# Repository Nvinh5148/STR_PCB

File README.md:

# STR_PCB

Custom PCB design for the low-level controller of the STR Robot autonomous vehicle platform.

## Overview

This repository contains the hardware design files for the custom controller board used in the STR Robot project. The board is designed to interface with the STM32-based firmware layer and provide the electrical bridge between the vehicle hardware and the ROS 2 autonomy stack.

This repository is part of the complete STR Robot simulation-to-reality system:
- custom PCB hardware
- STM32 micro-ROS firmware
- ROS 2 autonomy workspace
- real-world Ackermann robot deployment

## Board Preview

## Schematic Preview

**Schematic PDF:** [schematicf4.pdf](https://github.com/user-attachments/files/26848001/schematicf4.pdf)

## Repository Contents

- `f4_v2.kicad_sch` — KiCad schematic
- `f4_v2.kicad_pcb` — KiCad PCB layout
- `f4_v2.kicad_pro` — KiCad project file
- `Gerber_f4_v2/` — exported Gerber manufacturing files
- `Gerber_f4_v2.zip` — compressed Gerber package
- `f4_v2-backups/` — backup files

## Purpose

The board is designed as the low-level control hardware for the STR Robot platform. It supports the embedded controller responsible for:
- motor-related interfaces
- steering-related interfaces
- encoder and GPIO connections
- serial communication interfaces
- integration with the STM32 micro-ROS firmware layer

## System Role

This repository corresponds to the **hardware layer** of the full robot system:

`STR_PCB` → `microros_ws` → `ttbot_ws`

- **STR_PCB**: custom controller board
- **microros_ws**: STM32-based embedded firmware using micro-ROS
- **ttbot_ws**: high-level ROS 2 workspace for localization, planning, and navigation

## Hardware Interfaces

From the current board design, the PCB provides grouped connectors for:
- **GPIO**
- **ENCODER**
- **MOTOR**
- **UART / serial communication**
- power input / output terminals

## Toolchain

- KiCad for schematic and PCB design
- Standard Gerber export for PCB fabrication

## Manufacturing

To fabricate the board:
1. Open the project in KiCad
2. Review the schematic and PCB layout
3. Export or use the provided Gerber files in `Gerber_f4_v2/`
4. Submit the Gerber package to your PCB manufacturer

## Related Repositories

- Firmware: [`microros_ws`](https://github.com/Nvinh5148/microros_ws)
- ROS 2 autonomy stack: [`ttbot_ws`](https://github.com/Uyle-gif/ttbot_ws)

## Project Context

This board is part of the STR Robot simulation-to-reality development pipeline for an Ackermann-steered autonomous mobile robot.

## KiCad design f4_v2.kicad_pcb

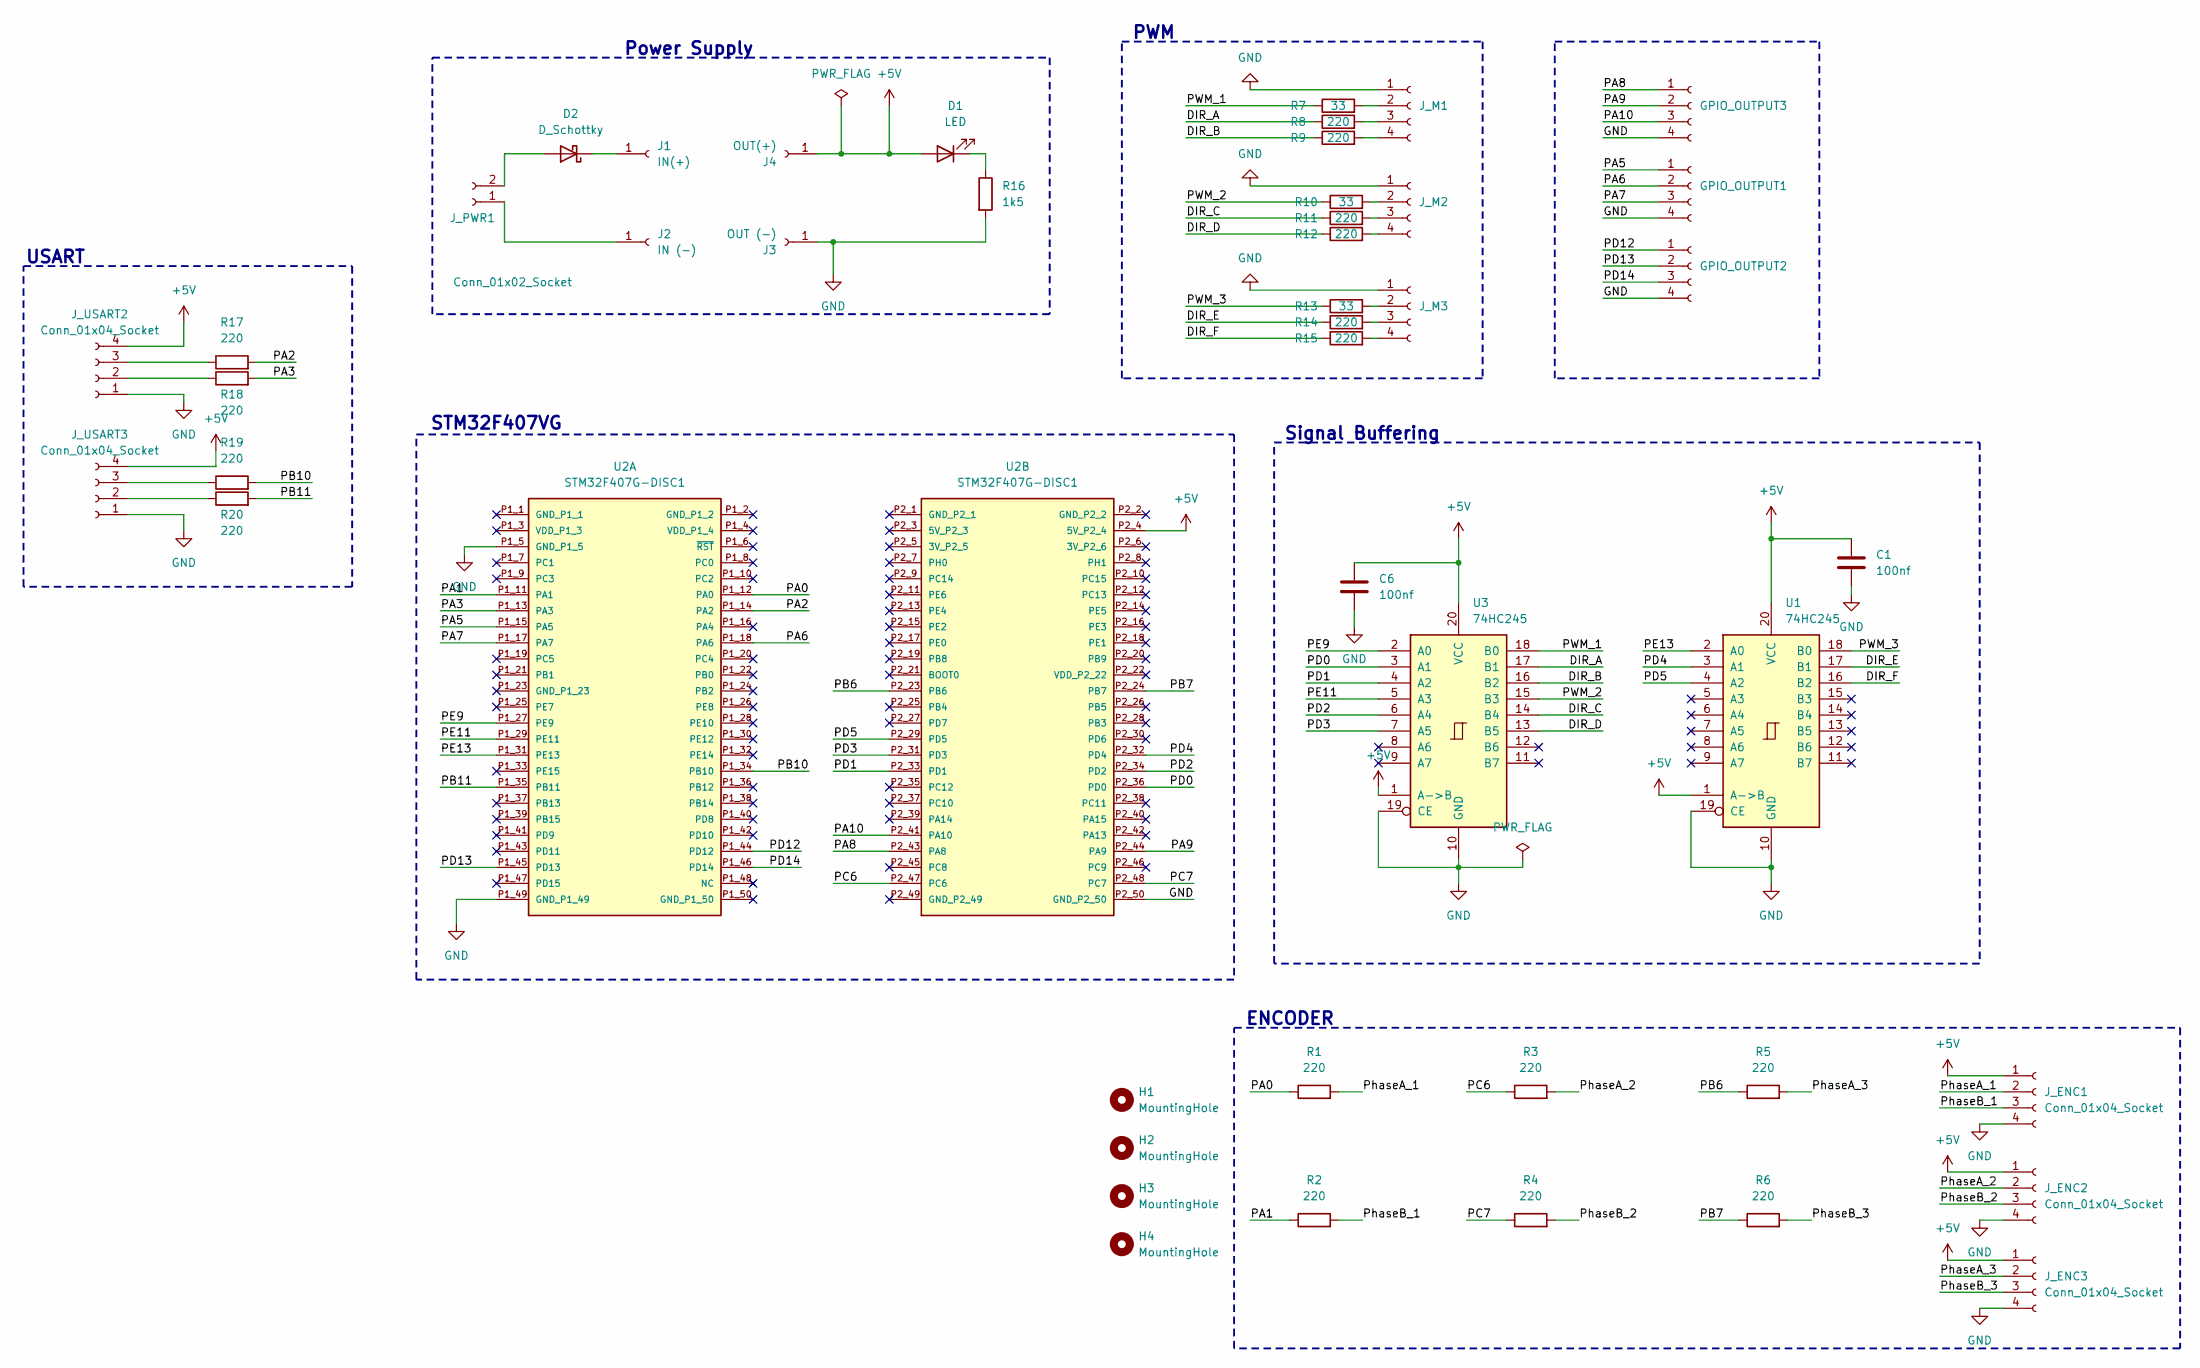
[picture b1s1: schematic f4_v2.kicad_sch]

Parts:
C1, C6: 100nf; C_0805_2012Metric
D1: LED; LED_0805_2012Metric
D2: D_Schottky; D_SMA
GPIO_OUTPUT1, GPIO_OUTPUT2, GPIO_OUTPUT3: JST_XH_B4B-XH-A_1x04_P2.50mm_Vertical
H1, H2, H3, H4: MountingHole; MountingHole_3.2mm_M3
J1: IN(+); PinHeader_1x01_P2.54mm_Vertical
J2: IN (-); PinHeader_1x01_P2.54mm_Vertical
J3: OUT (-); PinHeader_1x01_P2.54mm_Vertical
J4: OUT(+); PinHeader_1x01_P2.54mm_Vertical
J_ENC1, J_ENC2, J_ENC3: Conn_01x04_Socket; JST_XH_B4B-XH-A_1x04_P2.50mm_Vertical
J_M1, J_M2, J_M3: JST_XH_B4B-XH-A_1x04_P2.50mm_Vertical
J_PWR1: Conn_01x02_Socket; TerminalBlock_Phoenix_MKDS-1,5-2-5.08_1x02_P5.08mm_Horizont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
J_USART2, J_USART3: Conn_01x04_Socket; JST_XH_B4B-XH-A_1x04_P2.50mm_Vertical
R1, R2, R3, R4, R5, R6, R8, R9, R11, R12, R14, R15, R17, R18, R19, R20: 220; R_0805_2012Metric
R7, R10, R13: 33; R_0805_2012Metric
R16: 1k5; R_0805_2012Metric
U1, U3: 74HC245; TSSOP-20_4.4x6.5mm_P0.65mm
U2: STM32F407G-DISC1; MODULE_STM32F4DISCOVERY; PARTREV 7

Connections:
+5V: C1.1, C6.1, D1.2 (A), J4.1, J_ENC1.1, J_ENC2.1, J_ENC3.1, J_USART2.4, J_USART3.4, U1.1 (A->B), U1.20 (VCC), U2.P2_4 (5V_P2_4), U3.1 (A->B), U3.20 (VCC); also elsewhere on the board
/DIR_A: R8.1, U3.17 (B1)
/DIR_B: R9.1, U3.16 (B2)
/DIR_C: R11.1, U3.14 (B4)
/DIR_D: R12.1, U3.13 (B5)
/DIR_E: R14.1, U1.17 (B1)
/DIR_F: R15.1, U1.16 (B2)
/PA0: R1.1, U2.P1_12 (PA0)
/PA1: R2.1, U2.P1_11 (PA1)
/PA2: R17.2, U2.P1_14 (PA2)
/PA3: R18.2, U2.P1_13 (PA3)
/PA5: GPIO_OUTPUT1.1, U2.P1_15 (PA5)
/PA6: GPIO_OUTPUT1.2, U2.P1_18 (PA6)
/PA7: GPIO_OUTPUT1.3, U2.P1_17 (PA7)
/PA8: GPIO_OUTPUT3.1, U2.P2_43 (PA8)
/PA9: GPIO_OUTPUT3.2, U2.P2_44 (PA9)
/PA10: GPIO_OUTPUT3.3, U2.P2_41 (PA10)
/PB6: R5.1, U2.P2_23 (PB6)
/PB7: R6.1, U2.P2_24 (PB7)
/PB10: R19.2, U2.P1_34 (PB10)
/PB11: R20.2, U2.P1_35 (PB11)
/PC6: R3.1, U2.P2_47 (PC6)
/PC7: R4.1, U2.P2_48 (PC7)
/PD0: U2.P2_36 (PD0), U3.3 (A1)
/PD1: U2.P2_33 (PD1), U3.4 (A2)
/PD2: U2.P2_34 (PD2), U3.6 (A4)
/PD3: U2.P2_31 (PD3), U3.7 (A5)
/PD4: U1.3 (A1), U2.P2_32 (PD4)
/PD5: U1.4 (A2), U2.P2_29 (PD5)
/PD12: GPIO_OUTPUT2.1, U2.P1_44 (PD12)
/PD13: GPIO_OUTPUT2.2, U2.P1_45 (PD13)
/PD14: GPIO_OUTPUT2.3, U2.P1_46 (PD14)
/PE9: U2.P1_27 (PE9), U3.2 (A0)
/PE11: U2.P1_29 (PE11), U3.5 (A3)
/PE13: U1.2 (A0), U2.P1_31 (PE13)
/PWM_1: R7.1, U3.18 (B0)
/PWM_2: R10.1, U3.15 (B3)
/PWM_3: R13.1, U1.18 (B0)
/PhaseA_1: J_ENC1.2, R1.2
/PhaseA_2: J_ENC2.2, R3.2
/PhaseA_3: J_ENC3.2, R5.2
/PhaseB_1: J_ENC1.3, R2.2
/PhaseB_2: J_ENC2.3, R4.2
/PhaseB_3: J_ENC3.3, R6.2
GND: C1.2, C6.2, GPIO_OUTPUT1.4, GPIO_OUTPUT2.4, GPIO_OUTPUT3.4, J3.1, J_ENC1.4, J_ENC2.4, J_ENC3.4, J_M1.1, J_M2.1, J_M3.1, J_USART2.1, J_USART3.1, R16.2, U1.10 (GND), U1.19 (CE), U2.P1_5 (GND_P1_5), U2.P1_49 (GND_P1_49), U2.P2_50 (GND_P2_50), U3.10 (GND), U3.19 (CE); also elsewhere on the board
unnamed: D1.1 (K), R16.1
unnamed: D2.2 (A), J_PWR1.2
unnamed 47: D2.1 (K), J1.1; also elsewhere on the board
unnamed 48: J2.1, J_PWR1.1; also elsewhere on the board
unnamed: J_M1.2, R7.2
unnamed: J_M1.3, R8.2
unnamed: J_M1.4, R9.2
unnamed: J_M2.2, R10.2
unnamed: J_M2.3, R11.2
unnamed: J_M2.4, R12.2
unnamed: J_M3.2, R13.2
unnamed: J_M3.3, R14.2
unnamed: J_M3.4, R15.2
unnamed: J_USART2.2, R18.1
unnamed: J_USART2.3, R17.1
unnamed: J_USART3.2, R20.1
unnamed: J_USART3.3, R19.1

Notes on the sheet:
PWM
ENCODER
Signal Buffering
USART
STM32F407VG
Power Supply

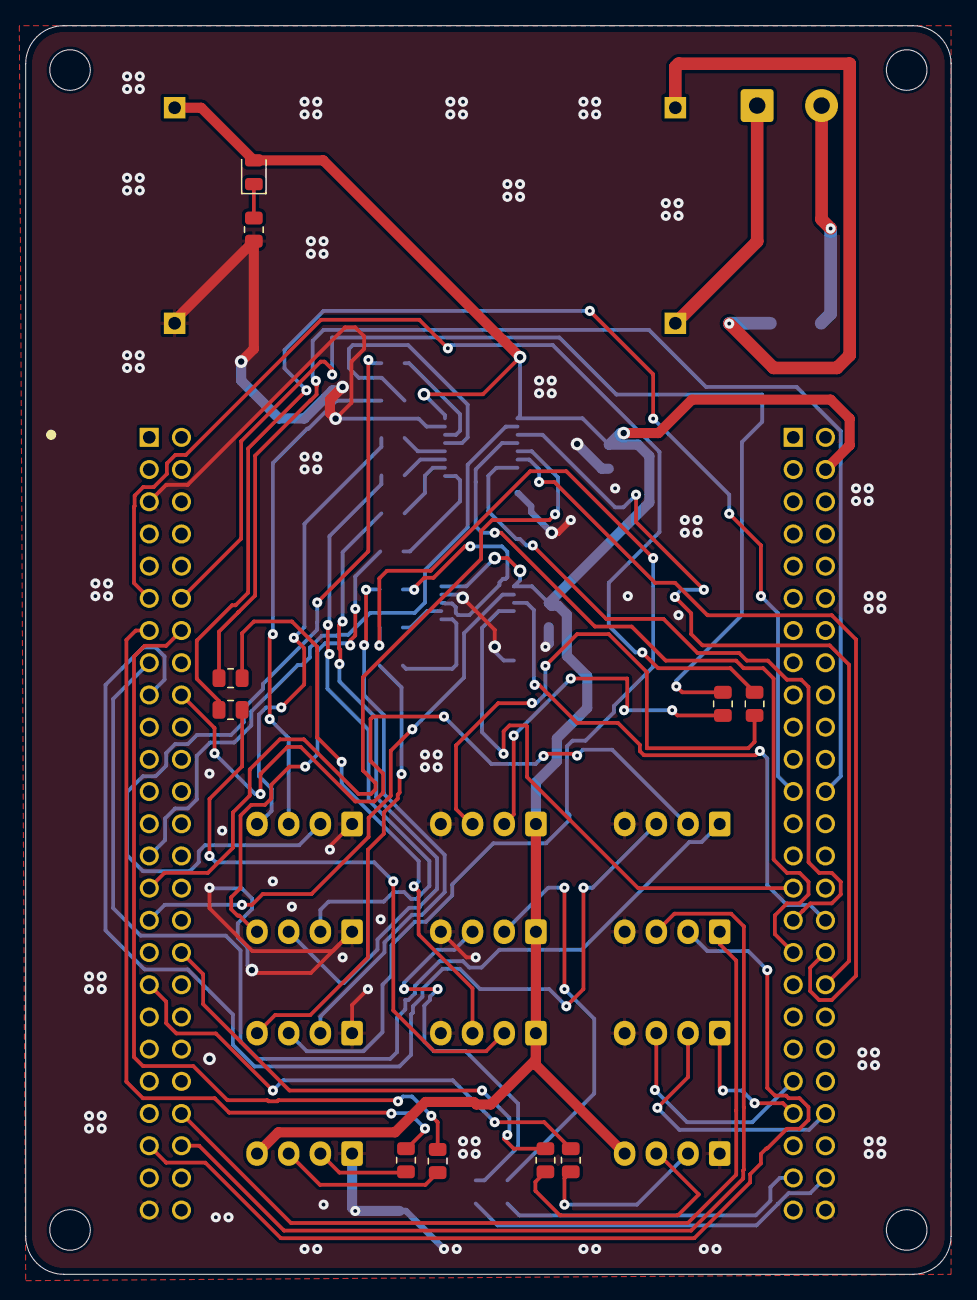
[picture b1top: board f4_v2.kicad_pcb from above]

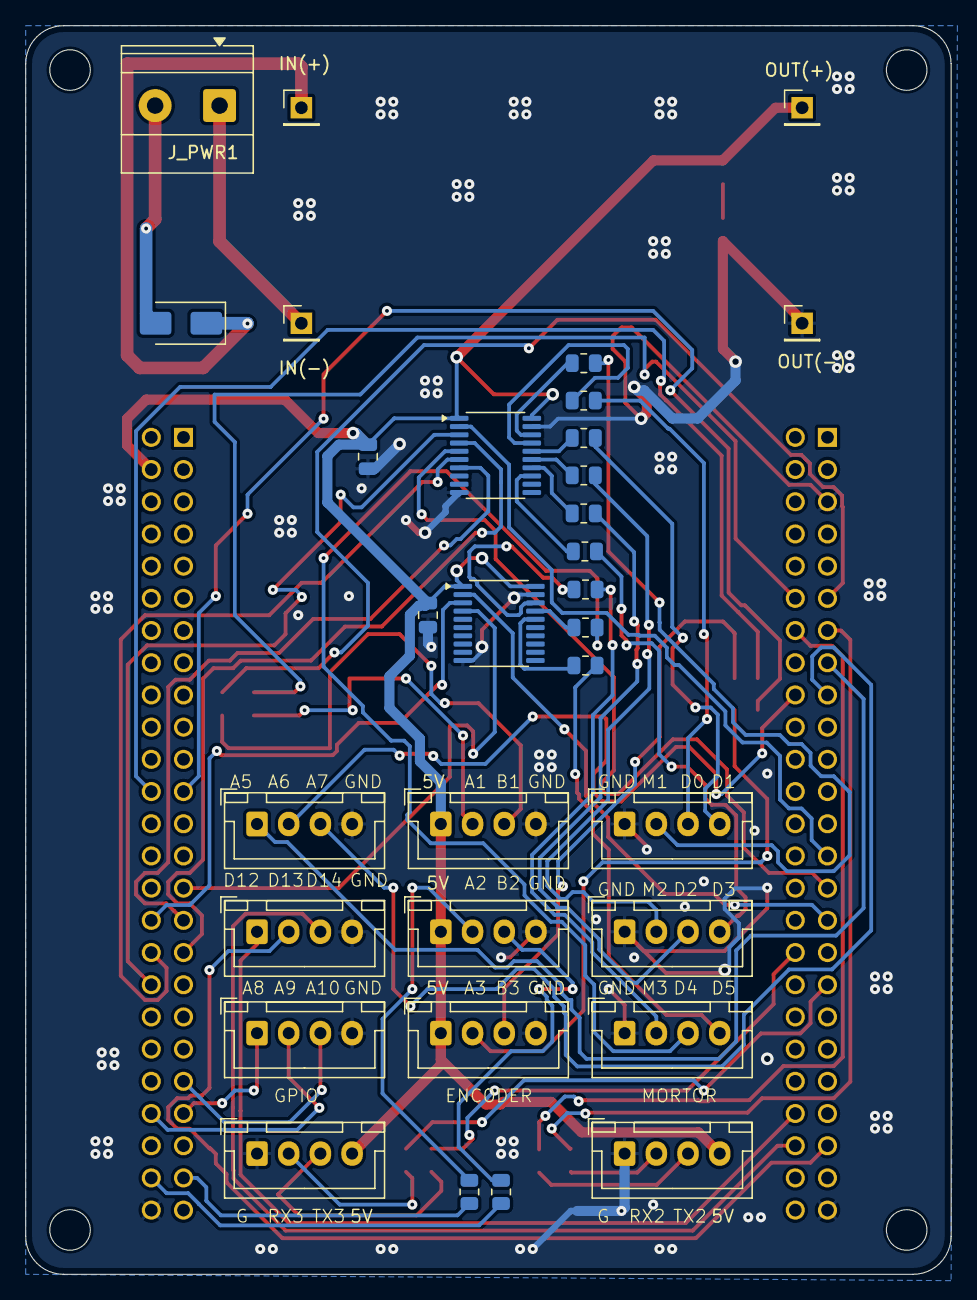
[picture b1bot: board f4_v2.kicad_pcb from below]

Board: 2 copper layers, 73.0 x 98.5 mm, 47 parts (32 on the bottom side), 62 nets.

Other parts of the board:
IN(+): IN(+); PinHeader_1x01_P2.54mm_Vertical
IN(-): IN (-); PinHeader_1x01_P2.54mm_Vertical
OUT(+): 5V; PinHeader_1x01_P2.54mm_Vertical
OUT(-): OUT (-); PinHeader_1x01_P2.54mm_Vertical

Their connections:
+5V: OUT(+).1; also elsewhere on the board
GND: OUT(-).1; also elsewhere on the board
unnamed 47: IN(+).1; also elsewhere on the board
unnamed 48: IN(-).1; also elsewhere on the board
